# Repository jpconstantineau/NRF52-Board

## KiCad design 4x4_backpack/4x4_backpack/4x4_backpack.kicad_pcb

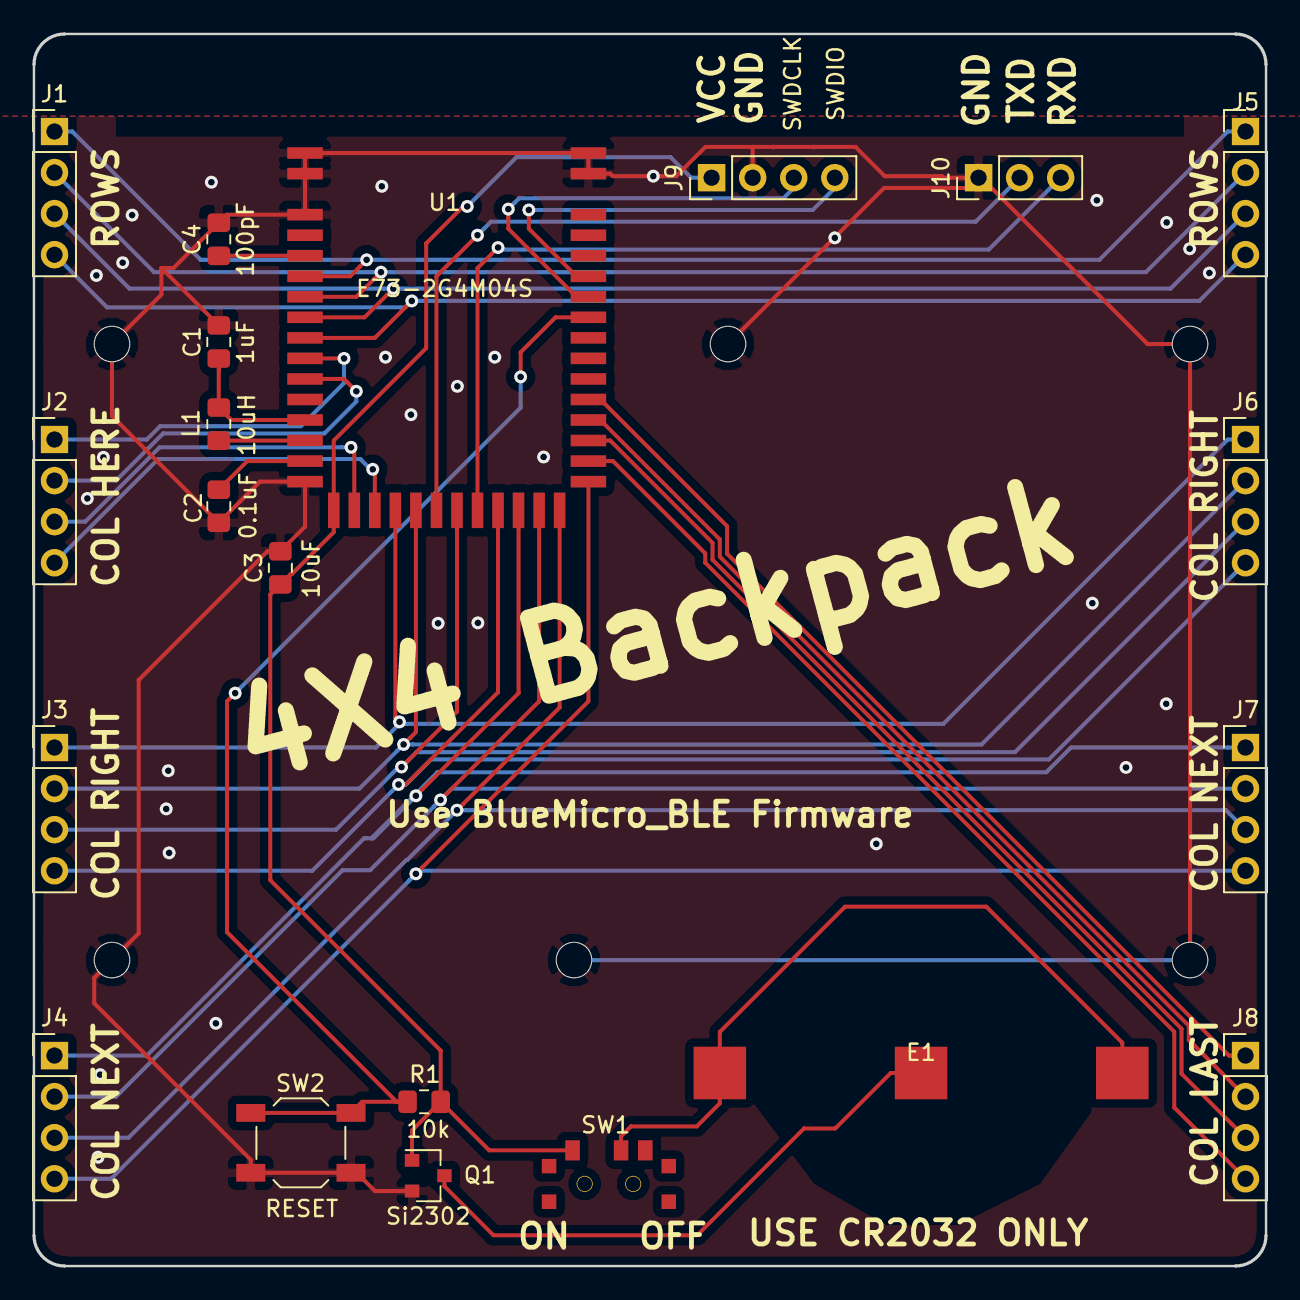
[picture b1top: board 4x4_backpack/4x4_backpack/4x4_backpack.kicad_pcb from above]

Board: 2 copper layers, 76.2 x 76.2 mm, 27 parts (0 on the bottom side), 33 nets.

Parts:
C1: 1uF; C_0805_2012Metric_Pad1.15x1.40mm_HandSolder
C2: 0.1uF; C_0805_2012Metric_Pad1.15x1.40mm_HandSolder
C3: 10uF; C_0805_2012Metric_Pad1.15x1.40mm_HandSolder
C4: 100pF; C_0805_2012Metric_Pad1.15x1.40mm_HandSolder
E1: Battery; C70373_CR2032
J1, J2, J3, J4, J5, J6, J7, J8, J9: Conn_01x04; PinHeader_1x04_P2.54mm_Vertical
J10: Conn_01x03; PinHeader_1x03_P2.54mm_Vertical
J11, J12, J13, J14, J15, J16: Conn_01x01; MountingHole_2.2mm_M2_ISO7380
L1: 10uH; C_0805_2012Metric_Pad1.15x1.40mm_HandSolder
Q1: Si2302; SOT-23
R1: 10k; C_0805_2012Metric_Pad1.15x1.40mm_HandSolder
SW1: SW_SPDT; SPDT_C128955
SW2: RESET; SW_TACT_ALPS_SKQGABE010
U1: E73-2G4M04S

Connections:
COL1: J2.1, U1.9
COL2: J2.2, U1.10
COL3: J2.3, U1.17
COL4: J2.4, U1.18
COL5: J3.1, J6.1, U1.19
COL6: J3.2, J6.2, U1.20
COL7: J3.3, J6.3, U1.22
COL8: J3.4, J6.4, U1.24
COL9: J4.1, J7.1, U1.25
COL10: J4.2, J7.2, U1.26
COL11: J4.3, J7.3, U1.27
COL12: J4.4, J7.4, U1.28
COL13: J8.1, U1.32
COL14: J8.2, U1.31
COL15: J8.3, U1.30
COL16: J8.4, U1.29
GND: C1.2, C2.2, C3.2, C4.2, J9.2, J10.1, J11.1, J12.1, J13.1, J14.1, J15.1, J16.1, Q1.2, SW2.1, U1.0, U1.1, U1.2, U1.15, U1.42, U1.43
unnamed: C1.1, L1.1, U1.12
unnamed: C2.1, U1.14
unnamed: C4.1, U1.4
unnamed: E1.1, SW1.2
unnamed: E1.2, Q1.3
unnamed: L1.2, U1.13
RESET: R1.2, SW2.2, U1.36
ROW1: J1.1, J5.1, U1.5
ROW2: J1.2, J5.2, U1.6
ROW3: J1.3, J5.3, U1.7
ROW4: J1.4, J5.4, U1.8
RXD: J10.3, U1.23
SWDCLK: J9.3, U1.37
SWDIO: J9.4, U1.38
TXD: J10.2, U1.21
VCC: C3.1, J9.1, Q1.1, R1.1, SW1.1, U1.16

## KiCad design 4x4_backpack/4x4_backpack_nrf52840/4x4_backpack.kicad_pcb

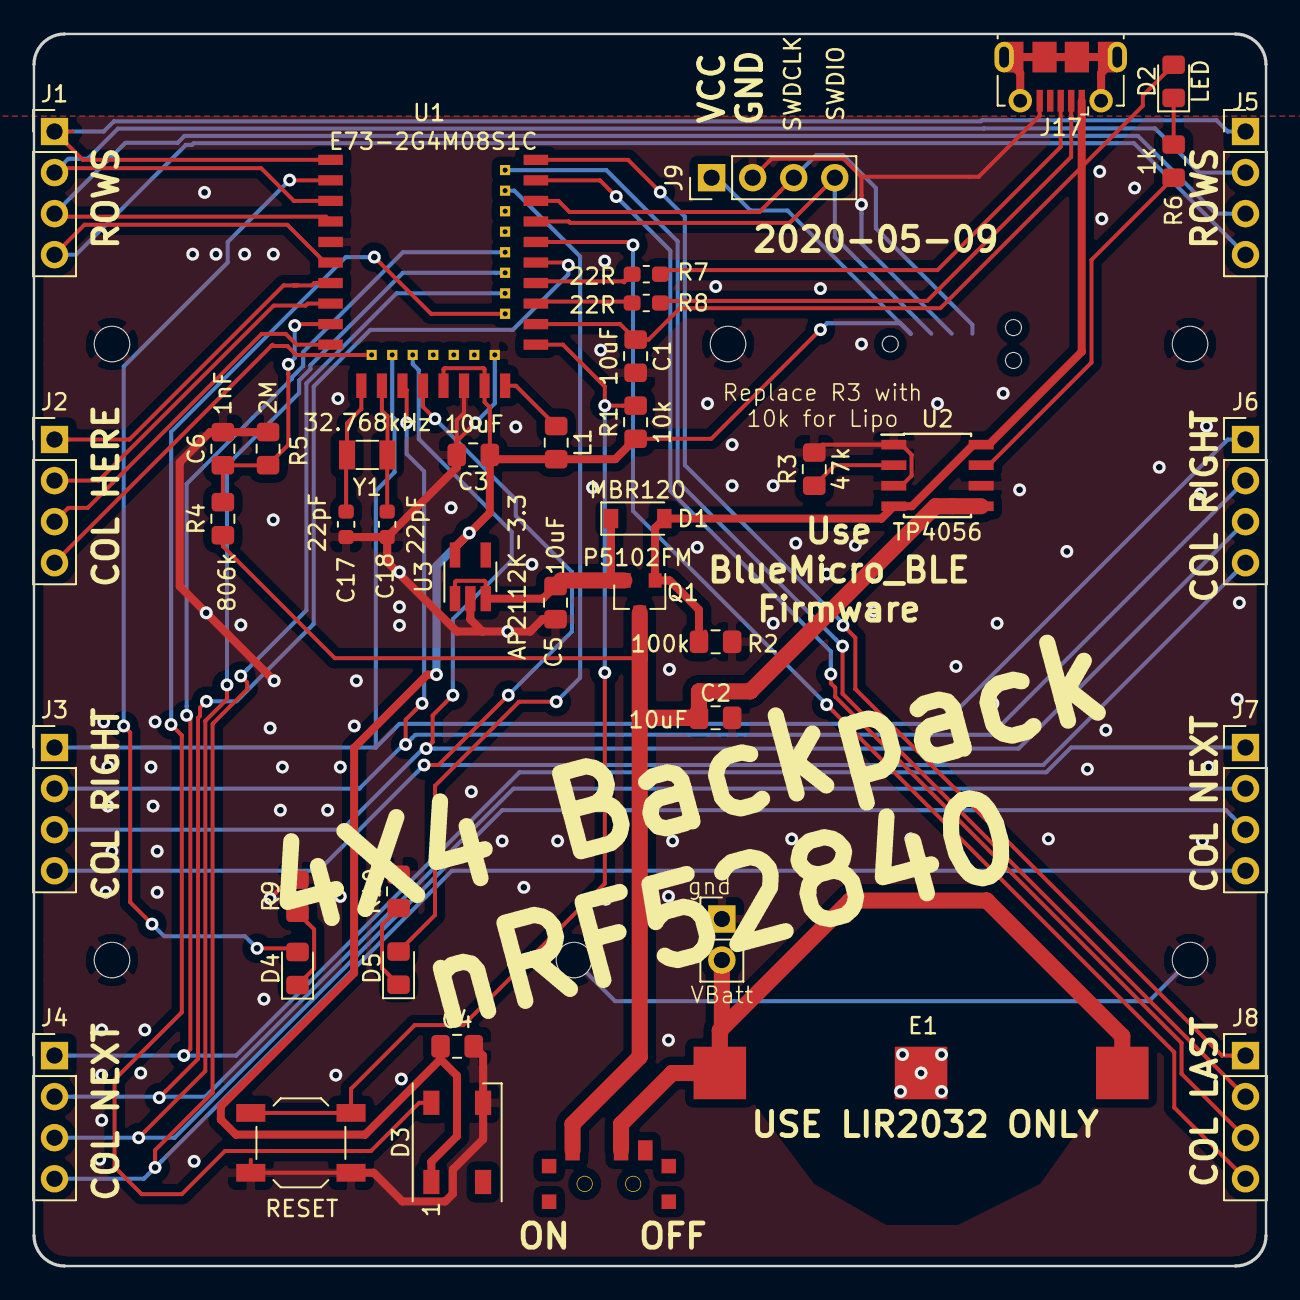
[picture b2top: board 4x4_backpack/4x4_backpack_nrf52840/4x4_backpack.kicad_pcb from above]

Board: 2 copper layers, 76.2 x 76.2 mm, 50 parts (1 on the bottom side), 45 nets.

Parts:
C1, C2, C3, C5: 10uF; C_0805_2012Metric_Pad1.15x1.40mm_HandSolder
C4: 100nF; C_0805_2012Metric_Pad1.15x1.40mm_HandSolder
C6: 1nF; C_0805_2012Metric_Pad1.15x1.40mm_HandSolder
C17, C18: 22pF; C_0603_1608Metric
D1: MBR120; D_SOD-123
D2, D4, D5: LED; LED_0805_2012Metric_Pad1.15x1.40mm_HandSolder
D3: WS2812B; LED_WS2812B_PLCC4_5.0x5.0mm_P3.2mm
E1: LR2032 - 4.2V; C70373_CR2032
J1, J2, J3, J4, J5, J6, J7, J8, J9: Conn_01x04; PinHeader_1x04_P2.54mm_Vertical
J10: TC2050; Tag-Connect_TC2050-IDC-NL_2x05_P1.27mm_Vertical
J11, J12, J13, J14, J15, J16: Conn_01x01; MountingHole_2.2mm_M2_ISO7380
J17: USB_B_Micro; USB_Micro-B_Molex-105017-0001
J18: Conn_01x02; PinHeader_1x02_P2.54mm_Vertical
L1: DNP; L_0805_2012Metric_Pad1.15x1.40mm_HandSolder
Q1: P5102FM; SOT-23
R1: 10k; R_0805_2012Metric_Pad1.15x1.40mm_HandSolder
R2: 100k; R_0805_2012Metric_Pad1.15x1.40mm_HandSolder
R3: 47k; R_0805_2012Metric_Pad1.15x1.40mm_HandSolder
R4: 806k; R_0805_2012Metric_Pad1.15x1.40mm_HandSolder
R5: 2M; R_0805_2012Metric_Pad1.15x1.40mm_HandSolder
R6, R9, R10: 1k; R_0805_2012Metric_Pad1.15x1.40mm_HandSolder
R7, R8: 22R; R_0603_1608Metric_Pad1.05x0.95mm_HandSolder
SW1: SW_SPDT; SPDT_C128955
SW2: RESET; SW_TACT_ALPS_SKQGABE010
U1: E73-2G4M08S1C; 2G4M08S1C
U2: TP4056; SOIC-8_3.9x4.9mm_P1.27mm
U3: AP2112K-3.3; SOT-23-5_HandSoldering
Y1: 32.768kHz; Crystal_SMD_3215-2Pin_3.2x1.5mm

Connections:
/Data+: R7.1, U1.31
/Data-: R8.1, U1.29
/P0.31: C6.1, R4.2, R5.1, U1.9
BLUE_LED: D4.2, U1.2
COL1: J2.1, U1.7
COL2: J2.2, U1.8
COL3: J2.3, U1.10
COL4: J2.4, U1.12
COL5: J3.1, J6.1, U1.14
COL6: J3.2, J6.2, U1.15
COL7: J3.3, J6.3, U1.16
COL8: J3.4, J6.4, U1.17
COL9: J4.1, J7.1, U1.34
COL10: J4.2, J7.2, U1.33
COL11: J4.3, J7.3, U1.32
COL12: J4.4, J7.4, U1.30
COL13: J8.1, U1.43
COL14: J8.2, U1.42
COL15: J8.3, U1.41
COL16: J8.4, U1.35
GND: C1.2, C2.2, C3.2, C4.2, C5.2, C6.2, C17.2, C18.2, D3.3, E1.2, J9.2, J10.3, J11.1, J12.1, J13.1, J14.1, J15.1, J16.1, J17.5, J18.1, R2.2, R3.2, R5.2, R9.2, R10.2, SW2.1, U1.5, U1.21, U1.24, U2.1, U2.3, U2.6, U3.2
unnamed: C2.1, Q1.3, R4.1, SW1.1, U2.5
unnamed: C5.1, D1.1, Q1.2, U3.1, U3.3
unnamed: C17.1, U1.11, Y1.1
unnamed: C18.1, U1.13, Y1.2
unnamed: D2.1, R6.1
unnamed: D4.1, R9.1
unnamed: D5.1, R10.1
unnamed: E1.1, J18.2, SW1.2
unnamed: J17.2, R8.2
unnamed: J17.3, R7.2
unnamed: L1.1, U1.25
unnamed: R3.1, U2.2
unnamed: R6.2, U2.7
RED_LED: D5.2, U1.40
RESET: R1.2, SW2.2, U1.26
ROW1: J1.1, J5.1, U1.1
ROW2: J1.2, J5.2, U1.3
ROW3: J1.3, J5.3, U1.4
ROW4: J1.4, J5.4, U1.6
SWDCLK: J9.3, J10.4, U1.39
SWDIO: J9.4, J10.2, U1.37
VBUS: C1.1, D1.2, D2.2, J17.1, Q1.1, R2.1, U1.27, U2.4, U2.8
VCC: C3.1, C4.1, D3.1, J9.1, J10.1, L1.2, R1.1, U1.19, U1.23, U3.5
WS2812: D3.4, U1.28

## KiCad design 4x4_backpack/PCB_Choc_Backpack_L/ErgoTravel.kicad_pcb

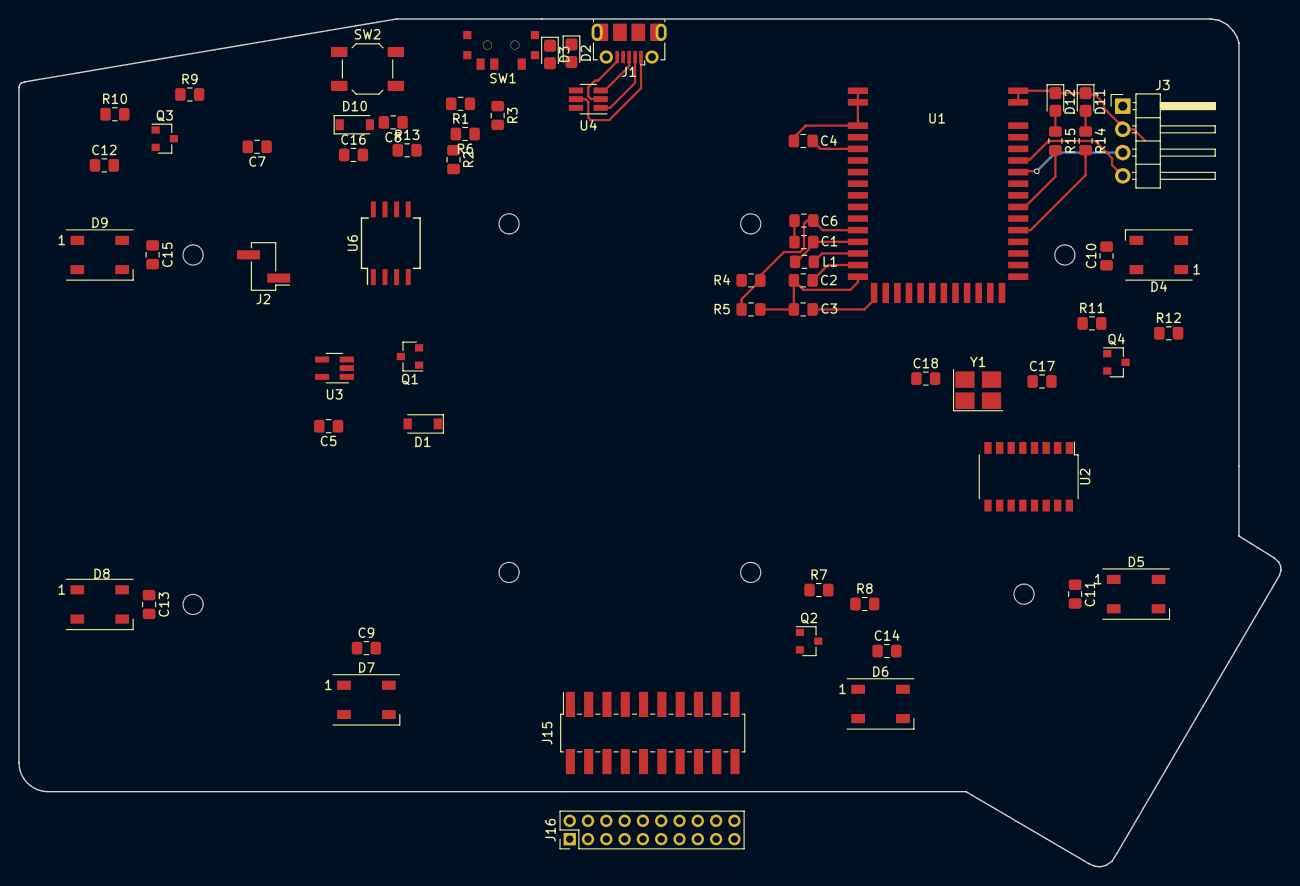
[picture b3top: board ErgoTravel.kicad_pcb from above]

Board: 2 copper layers, 137.9 x 92.7 mm, 71 parts (0 on the bottom side), 54 nets.

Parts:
C1: 1uF; C_0805_2012Metric_Pad1.15x1.40mm_HandSolder
C2, C9, C10, C11, C13, C14, C15, C16: 0.1uF; C_0805_2012Metric_Pad1.15x1.40mm_HandSolder
C3, C5, C7, C8, C12: 10uF; C_0805_2012Metric_Pad1.15x1.40mm_HandSolder
C4: 100pF; C_0805_2012Metric_Pad1.15x1.40mm_HandSolder
C6: 1nF; C_0805_2012Metric_Pad1.15x1.40mm_HandSolder
C17, C18: 22pF; C_0805_2012Metric_Pad1.15x1.40mm_HandSolder
D1: MBR120; D_SOD-123
D2, D3, D11, D12: LED; LED_0805_2012Metric_Castellated
D4, D5, D6, D7, D8, D9: WS2812B; LED_WS2812B_PLCC4_5.0x5.0mm_P3.2mm
D10: 1N4148; D_SOD-123
J1: USB_B_Micro; USB_Micro-B_Molex-105017-0001
J2: Conn_01x02; PinHeader_1x02_P2.54mm_Vertical_SMD_Pin1Left
J3: Conn_01x04; PinHeader_1x04_P2.54mm_Horizontal
J5, J6, J7, J8, J9, J10, J11, J12: Conn_01x01; MountingHole_2.2mm_M2_DIN965
J15: Conn_02x06_Counter_Clockwise; PinSocket_2x10_P2.00mm_Vertical_SMD
J16: Conn_02x06_Counter_Clockwise; PinHeader_2x10_P2.00mm_Vertical
L1: 10uH; L_0805_2012Metric_Pad1.15x1.40mm_HandSolder
Q1: TP0610T; SOT-23
Q2, Q3: P5102FM; SOT-23
Q4: SI2302; SOT-23
R1, R6, R14, R15: 2.2k; R_0805_2012Metric_Pad1.15x1.40mm_HandSolder
R2, R8, R10: 100k; R_0805_2012Metric_Pad1.15x1.40mm_HandSolder
R3, R11, R12, R13: 10k; R_0805_2012Metric_Pad1.15x1.40mm_HandSolder
R4: 806k; R_0805_2012Metric_Pad1.15x1.40mm_HandSolder
R5: 2M; R_0805_2012Metric_Pad1.15x1.40mm_HandSolder
R7, R9: 100; R_0805_2012Metric_Pad1.15x1.40mm_HandSolder
SW1: SW_SPDT; SPDT_C128955
SW2: SW_SPST; SW_TACT_ALPS_SKQGABE010
U1: E73-2G4M04S
U2: CH340G; SOP-16_4.4x10.4mm_P1.27mm
U3: AP2112K-3.3; SOT-23-5_HandSoldering
U4: USBLC6-4SC6Y; SOT-23-6_Handsoldering
U6: TP4056; SO-8_5.3x6.2mm_P1.27mm
Y1: 12MHz; Crystal_SMD_3225-4Pin_3.2x2.5mm_HandSoldering

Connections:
/4.2VSwitched: C9.1, C10.1, C11.1, C12.1, C13.1, C14.1, C15.1, D4.1, D5.1, D6.1, D7.1, D8.1, D9.1, Q3.3, R12.1
/DIN: Q4.1, R11.2
/DIN_4.2: D4.4, Q4.3, R12.2
/DTR: C16.2, U2.13
/Data+: J1.3, U2.5, U4.3
/Data-: J1.2, U2.6, U4.1
/LED: J15.18, Q2.3
/LED_PWM: R7.2, U1.20
/P0.16: R9.2, U1.31
/P0.17: R14.2, U1.32
/P0.19: R15.2, U1.34
/P0.31: C6.1, R4.1, R5.1, U1.11
/RESET: C16.1, D10.2, R13.2, SW2.1, U1.36
/RXD: U1.23, U2.2
/SWDCLK: J3.3, U1.37
/SWDIO: J3.4, U1.38
/TXD: U1.21, U2.3
/VBatt: C7.1, Q1.3, Q2.2, Q3.2, R4.2, SW1.2, U6.5
/VBus: C8.1, D1.2, J1.1, Q1.1, R1.2, R2.1, R6.1, U4.5, U6.4, U6.8
GND: C1.2, C2.2, C3.2, C4.2, C5.2, C6.2, C7.2, C8.2, C9.2, C10.2, C11.2, C12.2, C13.2, C14.2, C15.2, C17.2, C18.2, D4.3, D5.3, D6.3, D7.3, D8.3, D9.3, D11.1, D12.1, J1.5, J2.2, J3.2, J15.20, R2.2, R3.2, R5.2, SW2.2, U1.0, U1.1, U1.2, U1.15, U1.42, U1.43, U2.1, U3.2, U4.2, U6.1, U6.3, Y1.2, Y1.4
unnamed: C1.1, L1.1, U1.12
unnamed: C2.1, U1.14
unnamed: C4.1, U1.4
unnamed: C5.1, D1.1, Q1.2, U3.1, U3.3
unnamed: C17.1, U2.7, Y1.3
unnamed: C18.1, U2.8, Y1.1
unnamed: D2.1, U6.7
unnamed: D2.2, R1.1
unnamed: D3.1, U6.6
unnamed: D3.2, R6.2
unnamed: D4.2, D5.4
unnamed: D5.2, D6.4
unnamed: D6.2, D7.4
unnamed: D7.2, D8.4
unnamed: D8.2, D9.4
unnamed: D11.2, R14.1
unnamed: D12.2, R15.1
unnamed: J2.1, SW1.1
unnamed: L1.2, U1.13
unnamed: Q2.1, R7.1, R8.2
unnamed: Q3.1, R9.1, R10.2
unnamed: R3.1, U6.2
VCC: C3.1, D10.1, J3.1, Q4.2, R8.1, R10.1, R11.1, R13.1, U1.16, U2.4, U2.16, U3.5
col0: J15.1, U1.19
col1: J15.3, U1.18
col2: J15.5, U1.17
col3: J15.7, U1.27
col4: J15.9, U1.29
col5: J15.11, U1.28
col6: J15.13, U1.26
row0: J15.2, U1.8
row1: J15.4, U1.9
row2: J15.6, U1.10
row3: J15.8, U1.30

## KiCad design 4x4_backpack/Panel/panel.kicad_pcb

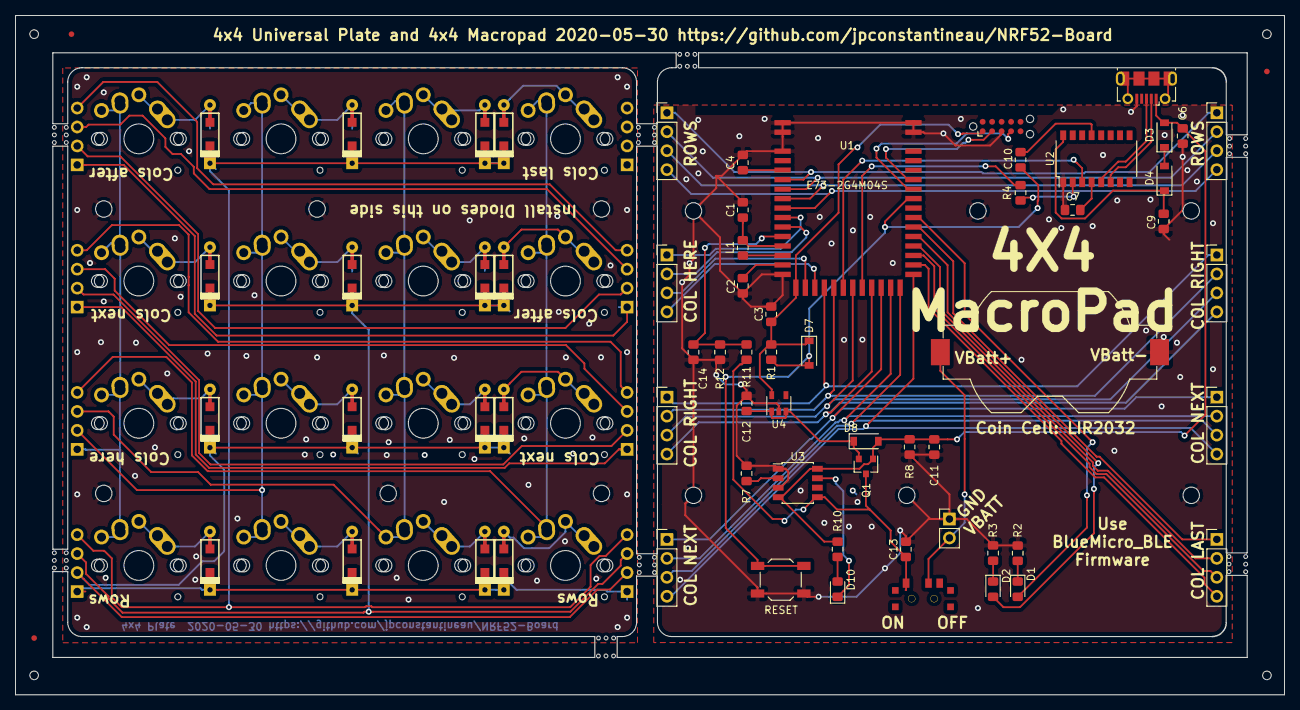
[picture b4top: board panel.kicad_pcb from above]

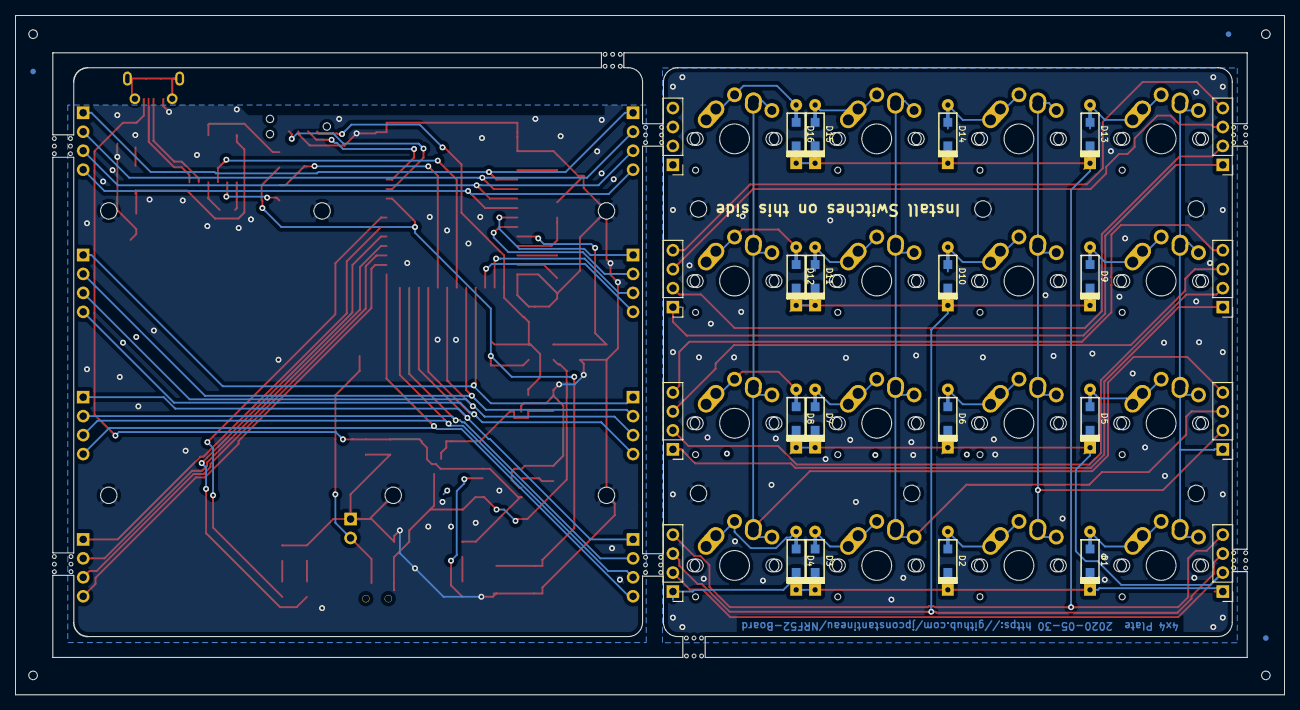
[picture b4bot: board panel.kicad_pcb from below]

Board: 2 copper layers, 170.0 x 91.0 mm, 104 parts (46 on the bottom side), 65 nets.

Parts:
BT1: Battery_Cell; Keystone_1058_1x2032-CoinCell
C1: 1uF; C_0805_2012Metric_Pad1.15x1.40mm_HandSolder
C2, C6, C7, C9, C10: 100nF; C_0805_2012Metric_Pad1.15x1.40mm_HandSolder
C3, C11, C12, C13: 10uF; C_0805_2012Metric_Pad1.15x1.40mm_HandSolder
C4: 100pF; C_0805_2012Metric_Pad1.15x1.40mm_HandSolder
C14: 1nF; C_0805_2012Metric_Pad1.15x1.40mm_HandSolder
D1, D2, D3, D4, D5, D6, D7, D8, D9, D10, D11, D12, D13, D14, D15, D16: DIODE; D_SOD123_axial-dual
D1#2: BLUE; LED_0805_2012Metric_Pad1.15x1.40mm_HandSolder
D2#2, D10#2: RED; LED_0805_2012Metric_Pad1.15x1.40mm_HandSolder
D3#2, D4#2, D7#2: 1N4148; D_SOD-123
D8#2: B5819W; D_SOD-123
J1, J1#2, J2, J2#2, J3, J3#2, J4, J4#2, J5, J5#2, J6, J6#2, J7, J7#2, J8, J8#2: Conn_01x04; PinHeader_1x04_P2.54mm_Vertical
J9: Conn_02x05_Counter_Clockwise; Tag-Connect_TC2050-IDC-NL_2x05_P1.27mm_Vertical
J10: Conn_01x02; PinHeader_1x02_P2.54mm_Vertical
J11, J11#2, J12, J12#2, J13, J13#2, J14, J14#2, J15, J15#2, J16, J16#2: Conn_01x01; MountingHole_2.2mm_M2_ISO7380
J17: USB_B_Micro; USB_Micro-B_Molex-105017-0001
L1: 10uH; C_0805_2012Metric_Pad1.15x1.40mm_HandSolder
Q1: SI2301CDS-T1-GE3; SOT-23
R1: 10k; C_0805_2012Metric_Pad1.15x1.40mm_HandSolder
R2, R3, R4, R10: 1k; R_0805_2012Metric_Pad1.15x1.40mm_HandSolder
R7: 10k; R_0805_2012Metric_Pad1.15x1.40mm_HandSolder
R8: 100k; R_0805_2012Metric_Pad1.15x1.40mm_HandSolder
R11: 806k; R_0805_2012Metric_Pad1.15x1.40mm_HandSolder
R12: 2M; R_0805_2012Metric_Pad1.15x1.40mm_HandSolder
Ref**: Val**; HOLE_JLCPCBA
Ref**#2, Ref**#3, Ref**#4: Val**; HOLE_JLCPCBA
S1, S2, S3, S4, S5, S6, S7, S8, S9, S10, S11, S12, S13, S14, S15, S16: CHERRY_MX; MX-Alps-Choc-1U
SW1: SW_SPDT; SPDT_C128955
SW2: RESET; SW_TACT_ALPS_SKQGABE010
U1: E73-2G4M04S
U2: CH340C; SOP-16_4.4x10.4mm_P1.27mm
U3: TP4056; SSOP-8_3.95x5.21x3.27mm_P1.27mm
U4: AP2112K-3.3; SOT-23-5

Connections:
BLUELED: D1#2.2, U1.34
COL1: J2.1, J2#2.1, S1.2, S5.2, S9.2, S13.2, U1.9
COL2: J2.2, J2#2.2, S2.2, S6.2, S10.2, S14.2, U1.10
COL3: J2.3, J2#2.3, S3.2, S7.2, S11.2, S15.2, U1.17
COL4: J2.4, J2#2.4, S4.2, S8.2, S12.2, S16.2, U1.18
COL5: J3.1, J3#2.1, J6.1, J6#2.1, U1.19
COL6: J3.2, J3#2.2, J6.2, J6#2.2, U1.20
COL7: J3.3, J3#2.3, J6.3, J6#2.3, U1.22
COL8: J3.4, J3#2.4, J6.4, J6#2.4, U1.24
COL9: J4.1, J4#2.1, J7.1, J7#2.1, U1.25
COL10: J4.2, J4#2.2, J7.2, J7#2.2, U1.26
COL11: J4.3, J4#2.3, J7.3, J7#2.3, U1.27
COL12: J4.4, J4#2.4, J7.4, J7#2.4, U1.28
COL13: J8#2.1, U1.33
COL14: J8#2.2, U1.31
COL15: J8#2.3, U1.30
COL16: J8#2.4, U1.29
DTR: C10.2, U2.13
GND: BT1.2, C1.2, C2.2, C3.2, C4.2, C6.2, C7.2, C9.2, C11.2, C12.2, C13.2, C14.2, J9.3, J10.1, J11.1, J11#2.1, J12.1, J12#2.1, J13.1, J13#2.1, J14.1, J14#2.1, J15.1, J15#2.1, J16.1, J16#2.1, J17.5, R2.2, R3.2, R7.1, R8.1, R12.2, SW2.1, U1.0, U1.1, U1.2, U1.15, U1.42, U1.43, U2.1, U3.1, U3.3, U4.2
unnamed: BT1.1, J10.2, SW1.2
unnamed: C1.1, L1.1, U1.12
unnamed: C2.1, U1.14
unnamed: C4.1, U1.4
unnamed: C7.1, U2.4
unnamed: C9.1, D4#2.1, U2.16
unnamed: C12.1, D8#2.1, Q1.2, U4.1, U4.3
unnamed: C14.1, R11.2, R12.1, U1.11
unnamed: D1#2.1, R2.1
unnamed: D1.2, S1.1
unnamed: D2#2.1, R3.1
unnamed: D2.2, S2.1
unnamed: D3#2.1, D4#2.2
unnamed: D3.2, S3.1
unnamed: D4.2, S4.1
unnamed: D5.2, S5.1
unnamed: D6.2, S6.1
unnamed: D7.2, S7.1
unnamed: D8.2, S8.1
unnamed: D9.2, S9.1
unnamed: D10#2.1, U3.7
unnamed: D10.2, D10#2.2, R10.2, S10.1
unnamed: D11.2, S11.1
unnamed: D12.2, S12.1
unnamed: D13.2, S13.1
unnamed: D14.2, S14.1
unnamed: D15.2, S15.1
unnamed: D16.2, S16.1
unnamed: J17.2, U2.6
unnamed: J17.3, U2.5
unnamed: L1.2, U1.13
unnamed: R4.1, U2.2
unnamed: R7.2, U3.2
REDLED: D2#2.2, U1.32
RESET: C10.1, D7#2.2, R1.2, SW2.2, U1.36
ROW1: D1.1, D2.1, D3.1, D4.1, J1.1, J1#2.1, J5.1, J5#2.1, U1.5
ROW2: D5.1, D6.1, D7.1, D8.1, J1.2, J1#2.2, J5.2, J5#2.2, U1.6
ROW3: D9.1, D10.1, D11.1, D12.1, J1.3, J1#2.3, J5.3, J5#2.3, U1.7
ROW4: D13.1, D14.1, D15.1, D16.1, J1.4, J1#2.4, J5.4, J5#2.4, U1.8
RXD: R4.2, U1.23
SWDCLK: J9.4, U1.37
SWDIO: J9.2, U1.38
TXD: U1.21, U2.3
VBATT: C13.1, Q1.3, R11.1, SW1.1, U3.5
VBUS: C6.1, C11.1, D3#2.2, D8#2.2, J17.1, Q1.1, R8.2, R10.1, U3.4, U3.8
VCC: C3.1, D7#2.1, J9.1, R1.1, U1.16, U4.5
